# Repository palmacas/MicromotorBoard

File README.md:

# Micromotor Board

Board to solder on micro metal gearmotors to avoid terminals damage. Includes a small ceramic capacitor and a two pin JST PH 2.0 connector.

---
More information:  
[Micromotor’s PCB](http://palmacas.com/micromotor-pcb/) [[Spanish]](http://palmacas.com/pcb-micromotor/)

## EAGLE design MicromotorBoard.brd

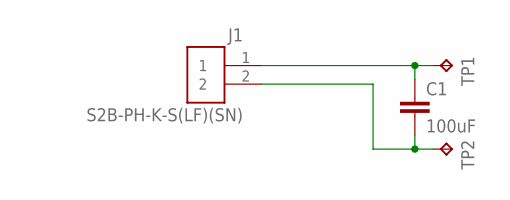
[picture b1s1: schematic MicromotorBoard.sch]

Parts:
C1: 100uF; C0805K
J1: S2B-PH-K-S(LF)(SN)
TP1, TP2: TPPAD1-17Y; P1-17Y

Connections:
unnamed: C1.1, J1.1, TP1.TP
unnamed: C1.2, J1.2, TP2.TP

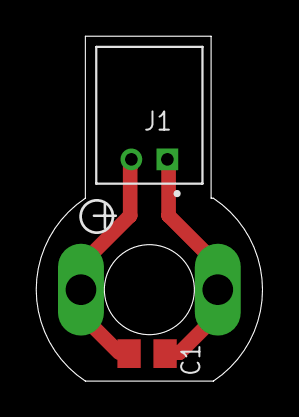
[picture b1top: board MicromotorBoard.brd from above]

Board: 2 copper layers, 12.6 x 19.2 mm, 4 parts (0 on the bottom side), 2 nets.

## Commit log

2023-01-13 PCB Update
